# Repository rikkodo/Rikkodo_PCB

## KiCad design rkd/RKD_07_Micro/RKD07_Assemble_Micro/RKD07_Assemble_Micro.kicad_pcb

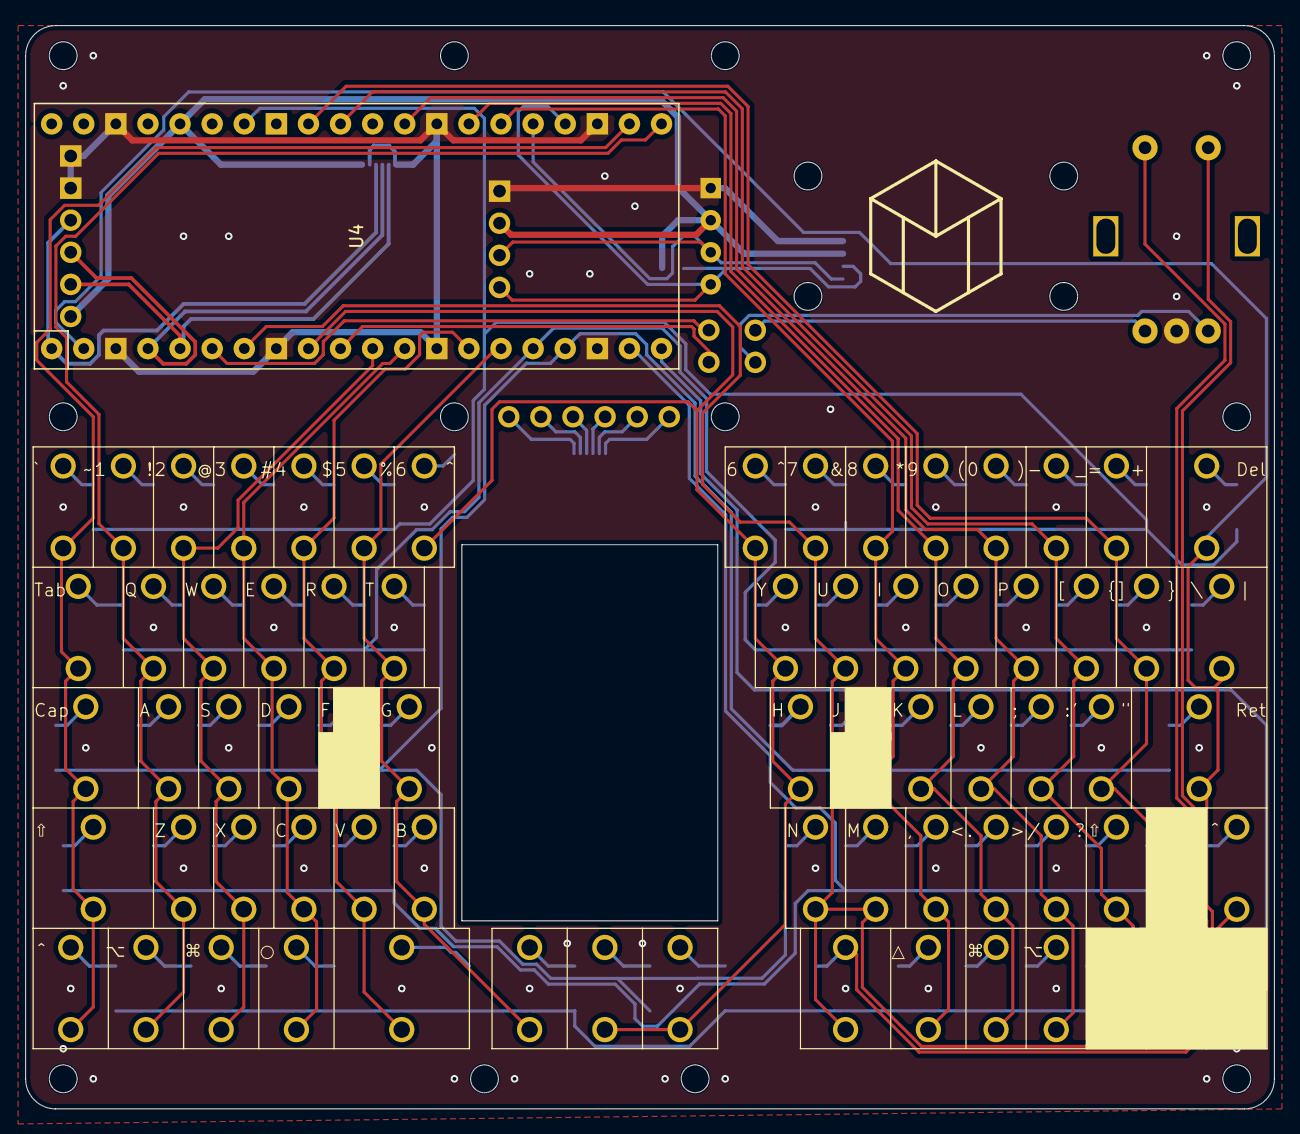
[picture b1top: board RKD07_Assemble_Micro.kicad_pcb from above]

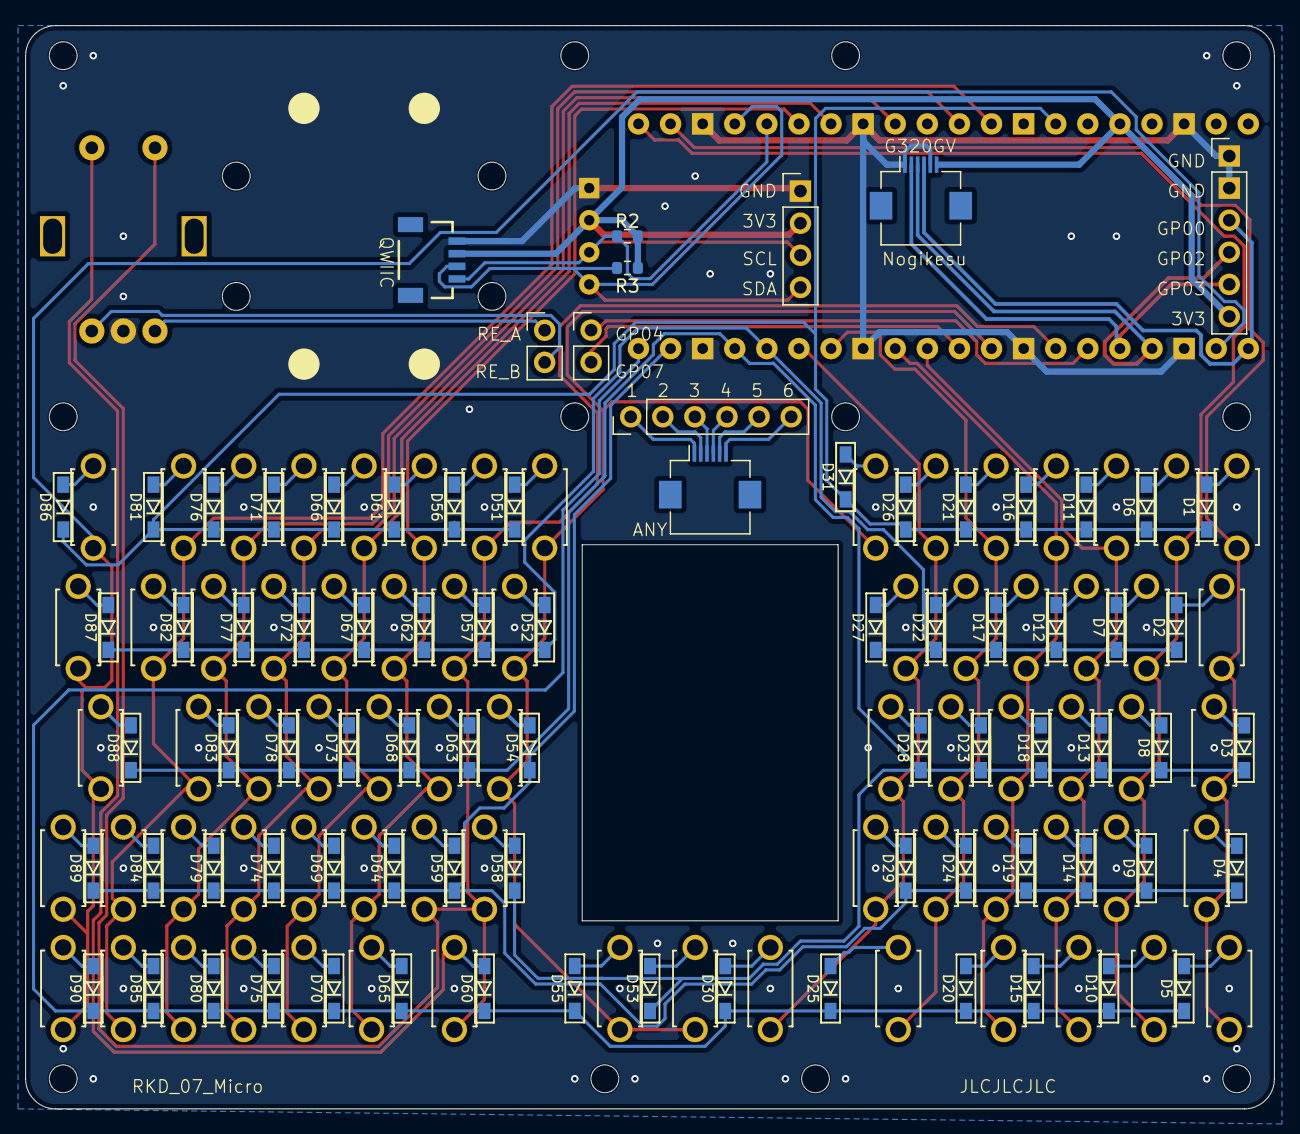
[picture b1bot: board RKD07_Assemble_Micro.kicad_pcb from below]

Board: 2 copper layers, 98.8 x 85.7 mm, 170 parts (10 on the bottom side), 107 nets.

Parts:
D1, D2, D3, D4, D5, D6, D7, D8, D9, D10, D11, D12, D13, D14, D15, D16, D17, D18, D19, D20, D21, D22, D23, D24, D25, D26, D27, D28, D29, D30, D31, D51, D52, D53, D54, D55, D56, D57, D58, D59, D60, D61, D62, D63, D64, D65, D66, D67, D68, D69, D70, D71, D72, D73, D74, D75, D76, D77, D78, D79, D80, D81, D82, D83, D84, D85, D86, D87, D88, D89, D90: D; Diode_SMD
J1, J5: Conn_01x06; Hirose_FH12-6S-0.5SH_1x06-1MP_P0.50mm_Horizontal
J2, J9: Conn_01x06; PinHeader_1x06_P2.54mm_Vertical
J3: Conn_01x04; PinHeader_1x04_P2.54mm_Vertical
J4, J6: Conn_01x02; PinHeader_1x02_P2.54mm_Vertical
J53: Qwiic_RA; JST_SMD_1.0mm-4_Black
OL2: OLED; OLED_center_display
Point1: Guard_Screw_Hall; rkd_Guard_Screw_Hall
R2, R3: 1kΩ; R_0603_1608Metric
Ref**: Val**; m2_Screw_Hole
Ref**#2, Ref**#3, Ref**#4, Ref**#5, Ref**#6, Ref**#7, Ref**#8, Ref**#9, Ref**#10, Ref**#11, Ref**#12, Ref**#13, Ref**#14: Val**; m2_Screw_Hole
SW1, SW6, SW7, SW8, SW9, SW11, SW12, SW13, SW14, SW16, SW17, SW18, SW19, SW21, SW22, SW23, SW24, SW26, SW27, SW28, SW29, SW31, SW51, SW52, SW54, SW56, SW57, SW58, SW59, SW61, SW62, SW63, SW64, SW66, SW67, SW68, SW69, SW70, SW71, SW72, SW73, SW74, SW75, SW76, SW77, SW78, SW79, SW80, SW81, SW82, SW83, SW84, SW85, SW89, SW90: SW_Push; rkd_pushsw_2_1u
SW2, SW60, SW87: SW_Push; rkd_pushsw_2_1.5u
SW3: SW_Push; rkd_pushsw_2_1.75u
SW4, SW86: SW_Push; rkd_pushsw_2_2u
SW5, SW10, SW15, SW20, SW30, SW53, SW55, SW65: SW_Push; rkd_pushsw_2_1.25u
SW25, SW88: SW_Push; rkd_pushsw_2_2.25u
SW49: RotaryEncoder_Switch; RotaryEncoder_EC11-Switch
U4: Pico; rkd_RPi_Pico_TH_NODBG

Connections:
3v3_R: J3.2, J5.6, J9.6, J53.2, OL2.3 (VCC), R2.1, R3.1, U4.36 (3V3)
COL0_R: SW1.2, SW2.2, SW3.2, SW4.2, SW5.2, U4.22 (GPIO17)
COL1_R: SW6.2, SW7.2, SW8.2, SW9.2, SW10.2, U4.21 (GPIO16)
COL2_R: SW11.2, SW12.2, SW13.2, SW14.2, SW15.2, U4.11 (GPIO8)
COL3_R: SW16.2, SW17.2, SW18.2, SW19.2, SW20.2, U4.12 (GPIO9)
COL4_R: SW21.2, SW22.2, SW23.2, SW24.2, SW25.2, U4.14 (GPIO10)
COL5_R: SW26.2, SW27.2, SW28.2, SW29.2, SW30.2, U4.15 (GPIO11)
COL6_R: SW31.2, SW51.2, SW52.2, SW53.2, SW54.2, SW55.2, U4.9 (GPIO6)
COL7_R: SW49.S1, SW56.2, SW57.2, SW58.2, SW59.2, SW60.2, U4.7 (GPIO5)
COL8_R: SW61.2, SW62.2, SW63.2, SW64.2, SW65.2, U4.26 (GPIO20)
COL9_R: SW66.2, SW67.2, SW68.2, SW69.2, SW70.2, U4.27 (GPIO21)
COL10_R: SW71.2, SW72.2, SW73.2, SW74.2, SW75.2, U4.29 (GPIO22)
COL11_R: SW76.2, SW77.2, SW78.2, SW79.2, SW80.2, U4.31 (GPIO26_ADC0)
COL12_R: SW81.2, SW82.2, SW83.2, SW84.2, SW85.2, U4.32 (GPIO27_ADC1)
COL13_R: SW86.2, SW87.2, SW88.2, SW89.2, SW90.2, U4.2 (GPIO1)
GND_R: J3.1, J5.1, J5.5, J9.1, J9.2, J53.1, OL2.4 (GND), SW49.C, U4.3 (GND), U4.8 (GND), U4.13 (GND), U4.18 (GND), U4.23 (GND), U4.28 (GND), U4.38 (GND)
GP00_R: J5.4, J9.3, U4.1 (GPIO0)
GP02_R: J5.3, J9.4, U4.4 (GPIO2)
GP03_R: J5.2, J9.5, U4.5 (GPIO3)
GP04_R: J4.1, U4.6 (GPIO4)
GP07_R: J4.2, U4.10 (GPIO7)
unnamed: D1.2 (A), SW1.1
unnamed: D2.2 (A), SW2.1
unnamed: D3.2 (A), SW3.1
unnamed: D4.2 (A), SW4.1
unnamed: D5.2 (A), SW5.1
unnamed: D6.2 (A), SW6.1
unnamed: D7.2 (A), SW7.1
unnamed: D8.2 (A), SW8.1
unnamed: D9.2 (A), SW9.1
unnamed: D10.2 (A), SW10.1
unnamed: D11.2 (A), SW11.1
unnamed: D12.2 (A), SW12.1
unnamed: D13.2 (A), SW13.1
unnamed: D14.2 (A), SW14.1
unnamed: D15.2 (A), SW15.1
unnamed: D16.2 (A), SW16.1
unnamed: D17.2 (A), SW17.1
unnamed: D18.2 (A), SW18.1
unnamed: D19.2 (A), SW19.1
unnamed: D20.2 (A), SW20.1
unnamed: D21.2 (A), SW21.1
unnamed: D22.2 (A), SW22.1
unnamed: D23.2 (A), SW23.1
unnamed: D24.2 (A), SW24.1
unnamed: D25.2 (A), SW25.1
unnamed: D26.2 (A), SW26.1
unnamed: D27.2 (A), SW27.1
unnamed: D28.2 (A), SW28.1
unnamed: D29.2 (A), SW29.1
unnamed: D30.2 (A), SW30.1
unnamed: D31.2 (A), SW31.1
unnamed: D51.2 (A), SW51.1
unnamed: D52.2 (A), SW52.1
unnamed: D53.2 (A), SW53.1
unnamed: D54.2 (A), SW54.1
unnamed: D55.2 (A), SW55.1
unnamed: D56.2 (A), SW56.1
unnamed: D57.2 (A), SW57.1
unnamed: D58.2 (A), SW58.1
unnamed: D59.2 (A), SW59.1
unnamed: D60.2 (A), SW49.S2, SW60.1
unnamed: D61.2 (A), SW61.1
unnamed: D62.2 (A), SW62.1
unnamed: D63.2 (A), SW63.1
unnamed: D64.2 (A), SW64.1
unnamed: D65.2 (A), SW65.1
unnamed: D66.2 (A), SW66.1
unnamed: D67.2 (A), SW67.1
unnamed: D68.2 (A), SW68.1
unnamed: D69.2 (A), SW69.1
unnamed: D70.2 (A), SW70.1
unnamed: D71.2 (A), SW71.1
unnamed: D72.2 (A), SW72.1
unnamed: D73.2 (A), SW73.1
unnamed: D74.2 (A), SW74.1
unnamed: D75.2 (A), SW75.1
unnamed: D76.2 (A), SW76.1
unnamed: D77.2 (A), SW77.1
unnamed: D78.2 (A), SW78.1
unnamed: D79.2 (A), SW79.1
unnamed: D80.2 (A), SW80.1
unnamed: D81.2 (A), SW81.1
unnamed: D82.2 (A), SW82.1
unnamed: D83.2 (A), SW83.1
unnamed: D84.2 (A), SW84.1
unnamed: D85.2 (A), SW85.1
unnamed: D86.2 (A), SW86.1
unnamed: D87.2 (A), SW87.1
unnamed: D88.2 (A), SW88.1
unnamed: D89.2 (A), SW89.1
unnamed: D90.2 (A), SW90.1
unnamed: J1.1, J2.1
unnamed: J1.2, J2.2
unnamed: J1.3, J2.3
unnamed: J1.4, J2.4
unnamed: J1.5, J2.5
unnamed: J1.6, J2.6
RE_A_R: J6.1, SW49.A
RE_B_R: J6.2, SW49.B
ROW0_R: D1.1 (K), D6.1 (K), D11.1 (K), D16.1 (K), D21.1 (K), D26.1 (K), D31.1 (K), D51.1 (K), D56.1 (K), D61.1 (K), D66.1 (K), D71.1 (K), D76.1 (K), D81.1 (K), D86.1 (K), U4.34 (GPIO28_ADC2)
ROW1_R: D2.1 (K), D7.1 (K), D12.1 (K), D17.1 (K), D22.1 (K), D27.1 (K), D52.1 (K), D57.1 (K), D62.1 (K), D67.1 (K), D72.1 (K), D77.1 (K), D82.1 (K), D87.1 (K), U4.16 (GPIO12)
ROW2_R: D3.1 (K), D8.1 (K), D13.1 (K), D18.1 (K), D23.1 (K), D28.1 (K), D53.1 (K), D58.1 (K), D63.1 (K), D68.1 (K), D73.1 (K), D78.1 (K), D83.1 (K), D88.1 (K), U4.17 (GPIO13)
ROW3_R: D4.1 (K), D9.1 (K), D14.1 (K), D19.1 (K), D24.1 (K), D29.1 (K), D54.1 (K), D59.1 (K), D64.1 (K), D69.1 (K), D74.1 (K), D79.1 (K), D84.1 (K), D89.1 (K), U4.19 (GPIO14)
ROW4_R: D5.1 (K), D10.1 (K), D15.1 (K), D20.1 (K), D25.1 (K), D30.1 (K), D55.1 (K), D60.1 (K), D65.1 (K), D70.1 (K), D75.1 (K), D80.1 (K), D85.1 (K), D90.1 (K), U4.20 (GPIO15)
SCL/TX_R: J3.3, J53.4, OL2.2 (SCL), R2.2, U4.25 (GPIO19)
SDA/SCK_R: J3.4, J53.3, OL2.1 (SDA), R3.2, U4.24 (GPIO18)

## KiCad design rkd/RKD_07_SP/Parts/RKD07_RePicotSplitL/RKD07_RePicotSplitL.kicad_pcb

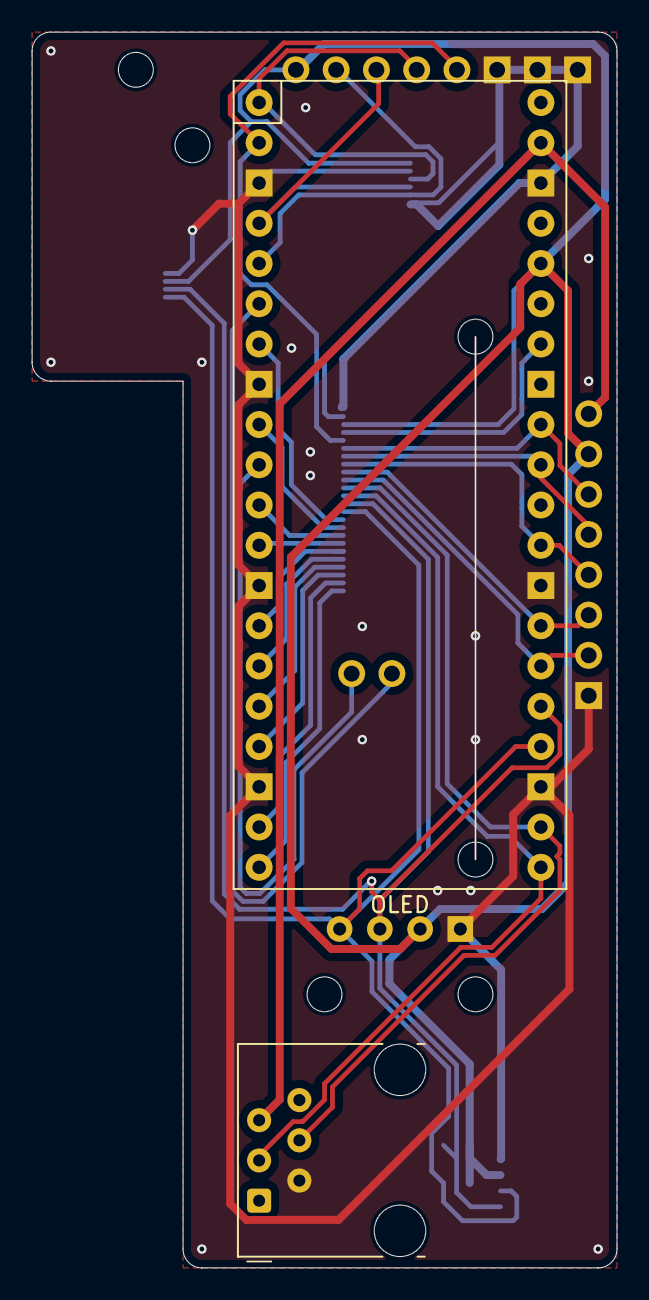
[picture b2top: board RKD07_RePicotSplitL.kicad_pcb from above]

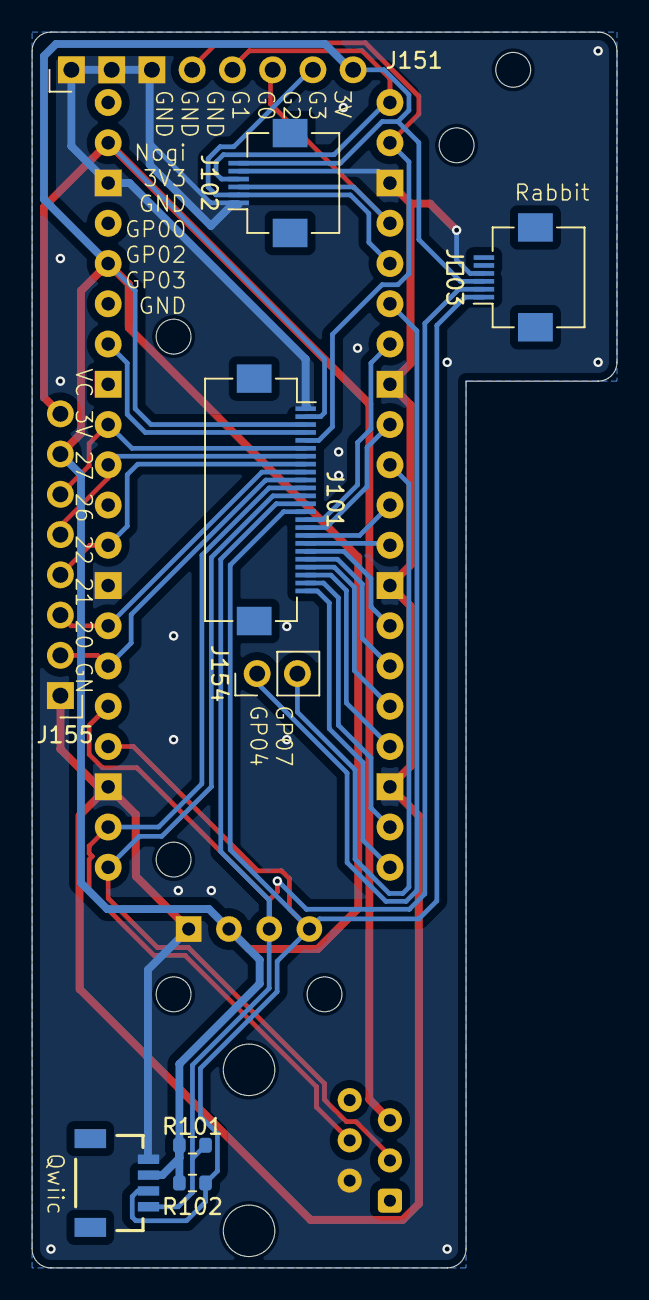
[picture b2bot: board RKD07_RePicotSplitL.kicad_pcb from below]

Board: 2 copper layers, 36.9 x 78.0 mm, 16 parts (9 on the bottom side), 29 nets.

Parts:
J101: Conn_01x24; Hirose_FH12-24S-0.5SH_1x24-1MP_P0.50mm_Horizontal
J102, J１03: Conn_01x06; Hirose_FH12-6S-0.5SH_1x06-1MP_P0.50mm_Horizontal
J151: Conn_01x06; PinHeader_1x08_P2.54mm_Vertical
J152: Qwiic_RA; JST_SMD_1.0mm-4_Black
J153: 6P6C; RJ12_Amphenol_54601-x06_Horizontal
J154: Conn_01x02_Socket; PinHeader_1x02_P2.54mm_Vertical
J155: Conn_01x08; PinHeader_1x08_P2.54mm_Vertical
OL101: OLED; OLED_center_display
Point1: Guard_Screw_Hall; rkd_Guard_Screw_Hall
R101, R102: 1kΩ; R_0603_1608Metric
Ref**: Val**; m2_Screw_Hole
Ref**#2: Val**; m2_Screw_Hole
U101: Pico; rkd_RPi_Pico_TH_NODBG
UnifiedW**: rkd_unified_wid_BTM

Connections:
3V3_L: J101.3, J102.6, J151.8, J152.2, J155.7, J１03.3, OL101.3 (VCC), R101.1, R102.1, U101.36 (3V3)
COL0_L: J101.15, U101.7 (GPIO5)
COL1_L: J101.16, U101.9 (GPIO6)
COL2_L: J101.17, U101.11 (GPIO8)
COL3_L: J101.18, U101.12 (GPIO9)
COL4_L: J101.19, U101.14 (GPIO10)
COL5_L: J101.20, U101.15 (GPIO11)
COL6_GP16_L: J101.12, J153.3, U101.21 (GPIO16)
COL7_GP17_L: J101.11, J153.4, U101.22 (GPIO17)
COL8_L: J101.10, J155.2, U101.26 (GPIO20)
COL9_L: J101.9, J155.3, U101.27 (GPIO21)
COL10_L: J101.8, J155.4, U101.29 (GPIO22)
COL11_L: J101.7, J155.5, U101.31 (GPIO26_ADC0)
COL12_L: J101.6, J155.6, U101.32 (GPIO27_ADC1)
COL13_GP01_NCS_L: J101.5, J151.4, U101.2 (GPIO1)
GND_L: J101.1, J102.1, J102.5, J151.1, J151.2, J151.3, J152.1, J153.2, J155.1, J１03.4, OL101.4 (GND), U101.3 (GND), U101.8 (GND), U101.13 (GND), U101.18 (GND), U101.23 (GND), U101.28 (GND), U101.38 (GND)
GP00_MISO_L: J102.4, J151.5, U101.1 (GPIO0)
GP02_SCLK_L: J102.3, J151.6, U101.4 (GPIO2)
GP03_MOSI_L: J102.2, J151.7, U101.5 (GPIO3)
GP04_L: J154.1, U101.6 (GPIO4)
GP07_L: J154.2, U101.10 (GPIO7)
ROW0_L: J101.4, U101.34 (GPIO28_ADC2)
ROW1_L: J101.21, U101.16 (GPIO12)
ROW2_L: J101.22, U101.17 (GPIO13)
ROW3_L: J101.23, U101.19 (GPIO14)
ROW4_L: J101.24, U101.20 (GPIO15)
SCL/TX_L: J101.13, J152.4, J１03.2, OL101.2 (SCL), R101.2, U101.25 (GPIO19)
SDA/SCK_L: J101.14, J152.3, J１03.1, OL101.1 (SDA), R102.2, U101.24 (GPIO18)
VCC_L: J101.2, J153.5, J155.8, U101.39 (VSYS)

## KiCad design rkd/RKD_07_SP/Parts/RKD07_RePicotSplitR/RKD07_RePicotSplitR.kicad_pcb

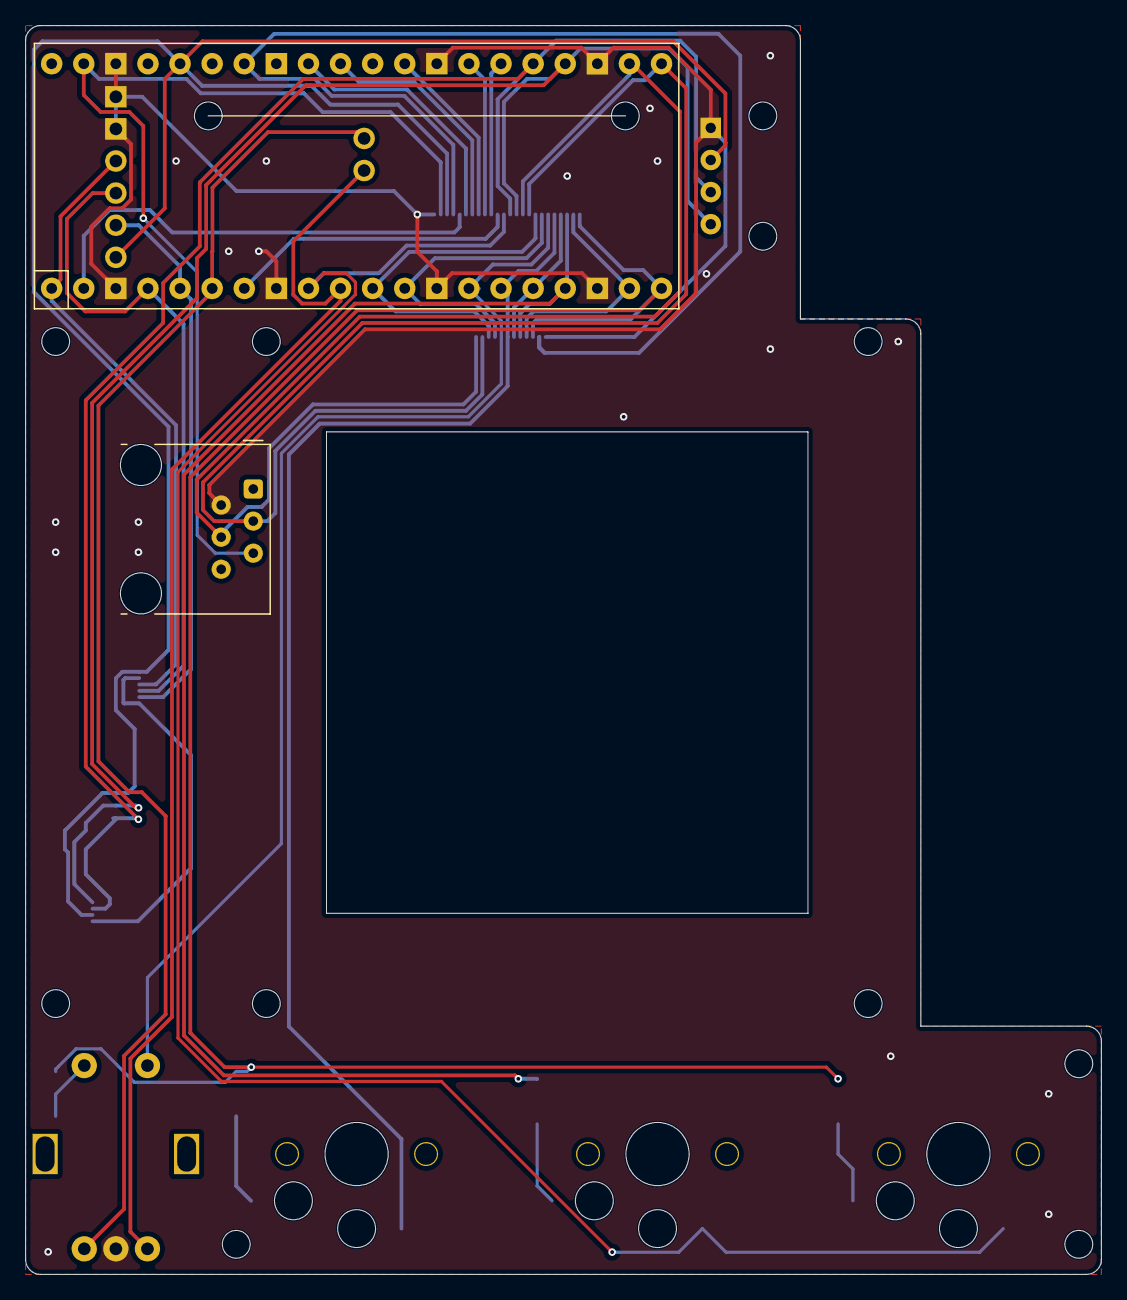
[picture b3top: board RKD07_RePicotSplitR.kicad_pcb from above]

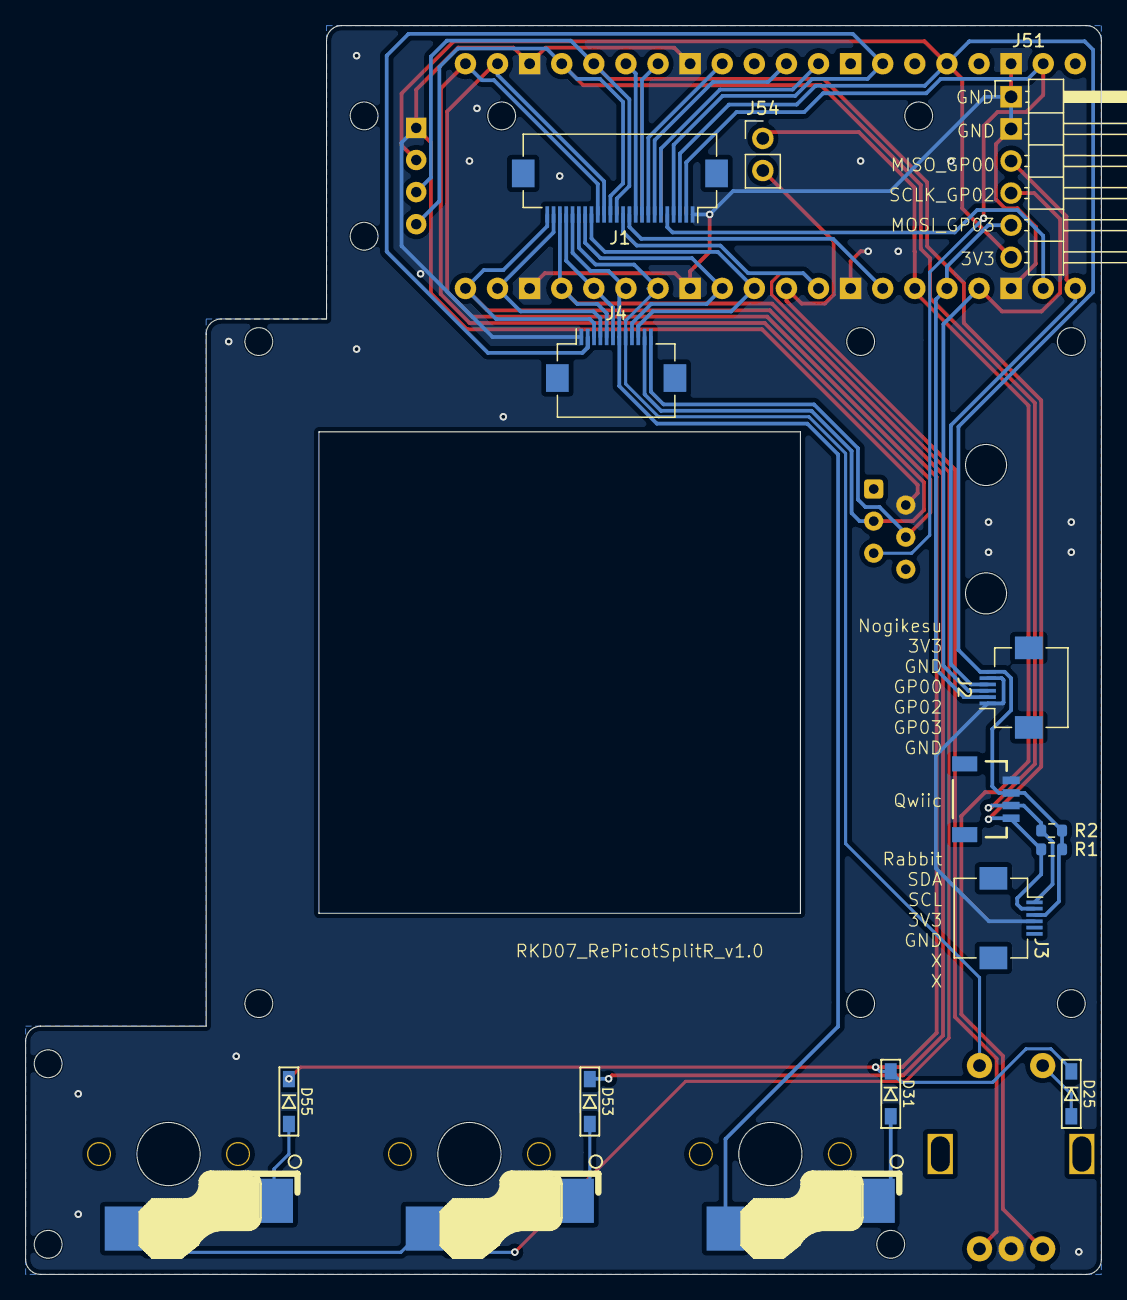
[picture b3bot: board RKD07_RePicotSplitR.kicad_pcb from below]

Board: 2 copper layers, 85.1 x 98.8 mm, 31 parts (9 on the bottom side), 33 nets.

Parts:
D25, D31, D53, D55: D; Diode_SMD
J1: Conn_01x24; Hirose_FH12-24S-0.5SH_1x24-1MP_P0.50mm_Horizontal
J2, J3: Conn_01x06; Hirose_FH12-6S-0.5SH_1x06-1MP_P0.50mm_Horizontal
J4: Conn_01x12; Hirose_FH12-12S-0.5SH_1x12-1MP_P0.50mm_Horizontal
J51: Conn_01x06; PinHeader_1x06_P2.54mm_Horizontal
J52: Qwiic_RA; JST_SMD_1.0mm-4_Black
J53: 6P6C; RJ12_Amphenol_54601-x06_Horizontal
J54: Conn_01x02_Socket; PinHeader_1x02_P2.54mm_Vertical
OL1: OLED; OLED_center_display
Point1: Guard_Screw_Hall; rkd_Guard_Screw_Hall
R1, R2: 1kΩ; R_0603_1608Metric
Ref**: Val**; m2_Screw_Hole
Ref**#2, Ref**#3, Ref**#4, Ref**#5, Ref**#6, Ref**#7, Ref**#8, Ref**#9: Val**; m2_Screw_Hole
SW25: RotaryEncoder_Switch; RotaryEncoder_EC11-Switch
SW31, SW53, SW55: SW_Push; rkd_Asm_ChocV1V2_Hotswap_1u
U1: Pico; rkd_RPi_Pico_TH_NODBG
UnifiedW**: rkd_unified_wid_BTM

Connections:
3V3_R: J1.3, J2.6, J3.3, J51.6, J52.2, OL1.3 (VCC), R1.1, R2.1, U1.36 (3V3)
COL0_GP17_R: J1.15, J4.12, J53.4, U1.22 (GPIO17)
COL1_GP16_R: J1.16, J4.11, J53.3, U1.21 (GPIO16)
COL2_R: J1.17, J4.10, U1.11 (GPIO8)
COL3_R: J1.18, J4.9, U1.12 (GPIO9)
COL4_R: J1.19, J4.8, SW25.S2, U1.14 (GPIO10)
COL5_R: J1.20, J4.7, SW31.2, U1.15 (GPIO11)
COL6_R: J1.12, SW53.2, SW55.2, U1.9 (GPIO6)
COL7_R: J1.11, U1.7 (GPIO5)
COL8_R: J1.10, U1.26 (GPIO20)
COL9_R: J1.9, U1.27 (GPIO21)
COL10_R: J1.8, U1.29 (GPIO22)
COL11_R: J1.7, U1.31 (GPIO26_ADC0)
COL12_R: J1.6, U1.32 (GPIO27_ADC1)
COL13_R: J1.5, U1.2 (GPIO1)
GND_R: J1.1, J2.1, J2.5, J3.4, J4.1, J51.1, J51.2, J52.1, J53.2, OL1.4 (GND), SW25.C, U1.3 (GND), U1.8 (GND), U1.13 (GND), U1.18 (GND), U1.23 (GND), U1.28 (GND), U1.38 (GND)
GP00_MISO_R: J2.4, J51.3, U1.1 (GPIO0)
GP02_SCLK_R: J2.3, J51.4, U1.4 (GPIO2)
GP03_MOSI_R: J2.2, J51.5, U1.5 (GPIO3)
GP04_RE_A_R: J54.1, SW25.A, U1.6 (GPIO4)
GP07_RE_B_R: J54.2, SW25.B, U1.10 (GPIO7)
unnamed: D25.2 (A), SW25.S1
unnamed: D31.2 (A), SW31.1
unnamed: D53.2 (A), SW53.1
unnamed: D55.2 (A), SW55.1
ROW0_R: J1.4, J4.2, U1.34 (GPIO28_ADC2)
ROW1_R: J1.21, J4.6, U1.16 (GPIO12)
ROW2_R: D53.1 (K), J1.22, J4.5, U1.17 (GPIO13)
ROW3_R: J1.23, J4.4, U1.19 (GPIO14)
ROW4_R: D25.1 (K), D31.1 (K), D55.1 (K), J1.24, J4.3, U1.20 (GPIO15)
SCL/TX_R: J1.13, J3.2, J52.4, OL1.2 (SCL), R1.2, U1.25 (GPIO19)
SDA/SCK_R: J1.14, J3.1, J52.3, OL1.1 (SDA), R2.2, U1.24 (GPIO18)
VCC_R: J1.2, J53.5, U1.39 (VSYS)
